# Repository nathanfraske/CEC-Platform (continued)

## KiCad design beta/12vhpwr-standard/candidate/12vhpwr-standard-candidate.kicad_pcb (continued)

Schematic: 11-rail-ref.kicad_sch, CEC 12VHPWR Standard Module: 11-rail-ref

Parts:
C22, C23: 100nF; C_0402_1005Metric; MPN CL05B104KO5NNNC; LCSC C1525
U4: REF3030; REF3030_DBZ3; MPN REF3030AIDBZR; LCSC C38423

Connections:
/VREF: C22.1, U4.2 (OUT); also elsewhere on the board

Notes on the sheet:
RAIL REF + SIDEBAND REF3030

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
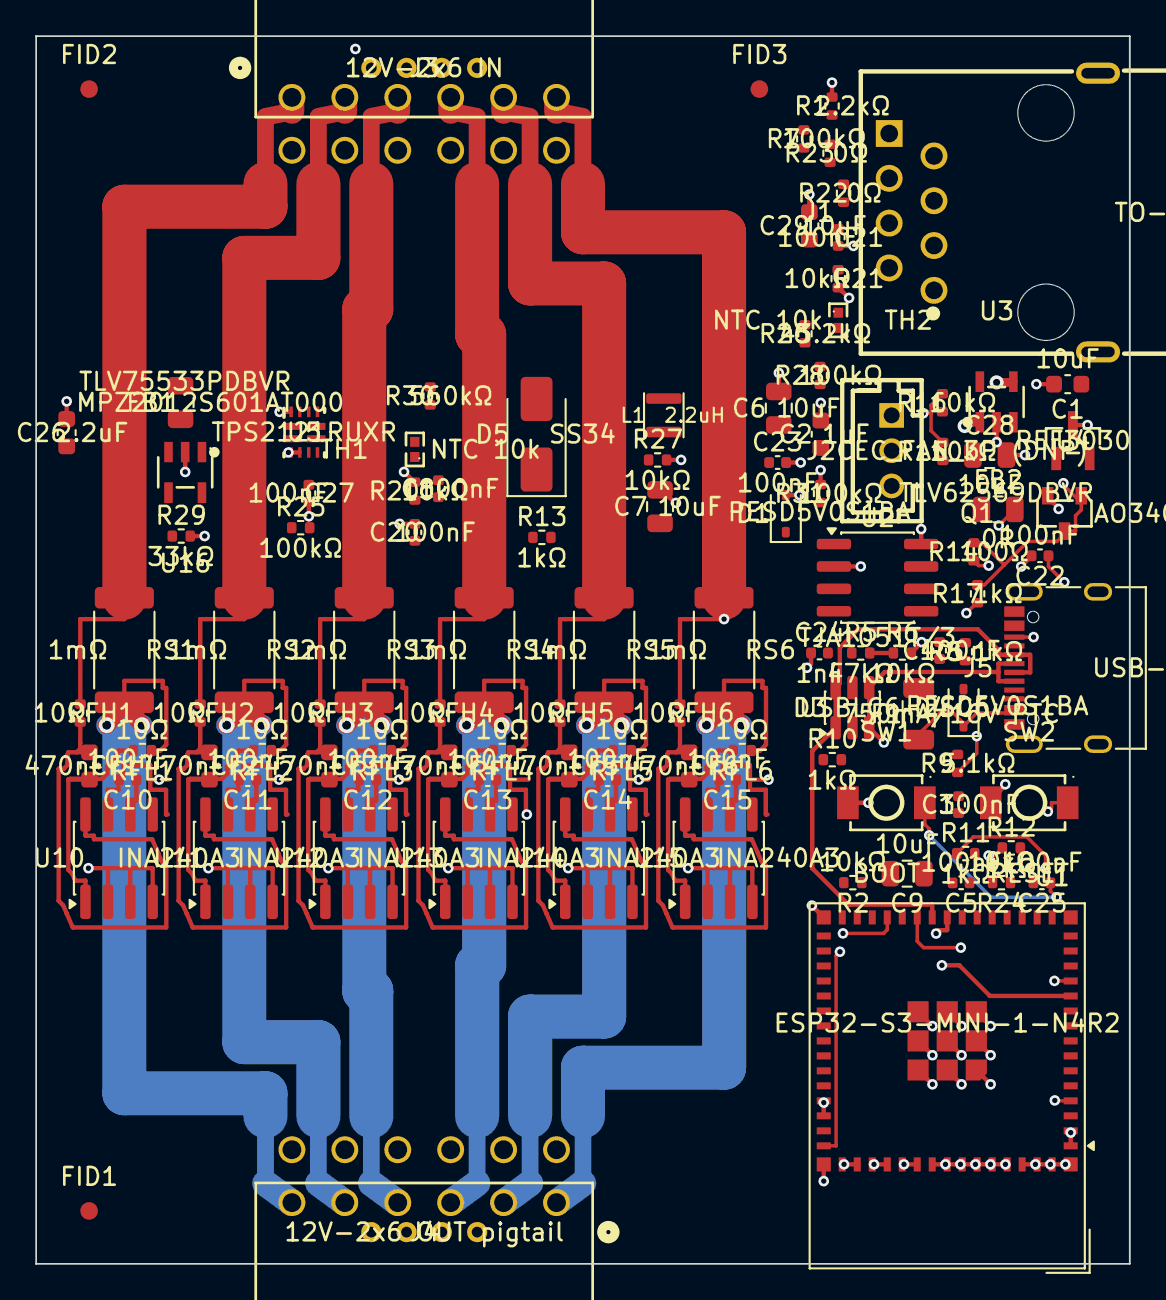
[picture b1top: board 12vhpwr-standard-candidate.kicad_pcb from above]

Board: 6 copper layers, 62.0 x 69.6 mm, 109 parts (0 on the bottom side), 74 nets.

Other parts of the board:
C29: 10uF; C_0603_1608Metric
FID1, FID2, FID3: Fiducial_1mm_Mask2mm
L1: 2.2uH; VLS252010HBX-2R2M-1
R30: 560kΩ; R_0402_1005Metric
R31: 100kΩ; R_0402_1005Metric
U3: TLV62569DBVR; SOT-23-5_L3.0-W1.7-P0.95-LS2.8-BL

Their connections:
+5VSB: U3.1, U3.4; also elsewhere on the board
/07-ldo/BUCK_FB_3V96: R30.2, R31.1, U3.5
/07-ldo/BUCK_SW_3V96: L1.1, U3.3

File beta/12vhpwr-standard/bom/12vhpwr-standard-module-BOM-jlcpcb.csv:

"Comment","Designator","Footprint","LCSC Part #"
"10uF","C1","cec-Capacitor_SMD:C_0603_1608Metric","C96446"
"1uF","C2","cec-Capacitor_SMD:C_0603_1608Metric","C29936"
"1nF","C24","cec-Capacitor_SMD:C_0402_1005Metric","C76947"
"2.2uF","C26","cec-Capacitor_SMD:C_0603_1608Metric","C23630"
"100nF","C3,C4,C5,C8,C10,C11,C12,C13,C14,C15,C20,C21,C22,C23,C25,C27","cec-Capacitor_SMD:C_0402_1005Metric","C1525"
"10uF","C6,C7,C9,C28","cec-Capacitor_SMD:C_0805_2012Metric","C15850"
"470nF","CF1,CF2,CF3,CF4,CF5,CF6","cec-Capacitor_SMD:C_0603_1608Metric","C1623"
"PESD5V0S1BA","D1,D4","cec-Diode_SMD:D_SOD-323","C5261083"
"USBLC6-2SC6","D3","cec-Package_TO_SOT_SMD:SOT-23-6","C2687116"
"SS34","D5","cec-Diode_SMD:D_SMA","C8678"
"750mA/16V PTC","F1","cec-Resistor_SMD:R_1206_3216Metric","C371166"
"MPZ2012S601AT000","FB1","cec-Capacitor_SMD:C_0805_2012Metric","C21519"
"0R","FB2","cec-Capacitor_SMD:C_0805_2012Metric","C17477"
"TO-HUB","J1","cec:RJ45_FTP_Shielded_Horizontal","C2683360"
"12V-2x6 IN","J3","cec:CEC_12V2x6_Horizontal",""
"12V-2x6 OUT pigtail","J4","cec:CEC_12V2x6_Horizontal",""
"USB-C 2.0","J5","cec-Connector_USB:USB_C_Receptacle_XKB_U262-16XN-4BVC11","C319148"
"AO3400A","Q1","cec-Package_TO_SOT_SMD:SOT-23-3_L2.9-W1.3-P1.90-LS2.4-BR","C20917"
"2.2kΩ","R1","cec-Resistor_SMD:R_0402_1005Metric","C25879"
"1kΩ","R10,R11,R12,R13,R17","cec-Resistor_SMD:R_0402_1005Metric","C11702"
"100Ω","R14","cec-Resistor_SMD:R_0402_1005Metric","C106233"
"10kΩ","R2,R15,R16,R20,R21,R24,R27","cec-Resistor_SMD:R_0402_1005Metric","C25744"
"0Ω","R22,R23","cec-Resistor_SMD:R_0402_1005Metric","C17168"
"43.2kΩ","R26","cec-Resistor_SMD:R_0402_1005Metric","C25894"
"33kΩ","R29","cec-Resistor_SMD:R_0402_1005Metric","C25779"
"47kΩ","R5","cec-Resistor_SMD:R_0402_1005Metric","C728561"
"10kΩ","R6","cec-Resistor_SMD:R_0402_1005Metric","C190095"
"100kΩ","R7,R25,R28","cec-Resistor_SMD:R_0402_1005Metric","C25741"
"5.1kΩ","R8,R9","cec-Resistor_SMD:R_0402_1005Metric","C25905"
"10Ω","RFH1,RFH2,RFH3,RFH4,RFH5,RFH6,RFL1,RFL2,RFL3,RFL4,RFL5,RFL6","cec-Resistor_SMD:R_0402_1005Metric","C705642"
"1mΩ","RS1,RS2,RS3,RS4,RS5,RS6","cec-Resistor_SMD:R_2512_6332Metric","C4175647"
"BOOT","SW1","cec-Button_Switch_SMD:TS-1088-AR02016","C720477"
"RESET","SW2","cec-Button_Switch_SMD:TS-1088-AR02016","C720477"
"NTC 10k","TH1,TH2","cec-Resistor_SMD:NTC_0402_1005Metric","C77131"
"ESP32-S3-MINI-1-N4R2","U1","cec-RF_Module:ESP32-S2-MINI-1_NoAntKeepout","C3013941"
"INA240A3","U10,U11,U12,U13,U14,U15","cec-Package_SO:SOIC-8_3.9x4.9mm_P1.27mm","C2060584"
"TLV75533PDRVR","U16","cec-Package_SON:WSON-6-1EP_2x2mm_P0.65mm_EP1x1.6mm","C2861750"
"TJA1051T/3","U2","cec-Package_SO:SOIC-8_3.9x4.9mm_P1.27mm","C38695"
"REF3030","U4","cec-Package_TO_SOT_SMD:REF3030_DBZ3","C38423"
"TPS2121RUXR","U5","cec-Package_DFN_QFN:RUX0012A","C485916"

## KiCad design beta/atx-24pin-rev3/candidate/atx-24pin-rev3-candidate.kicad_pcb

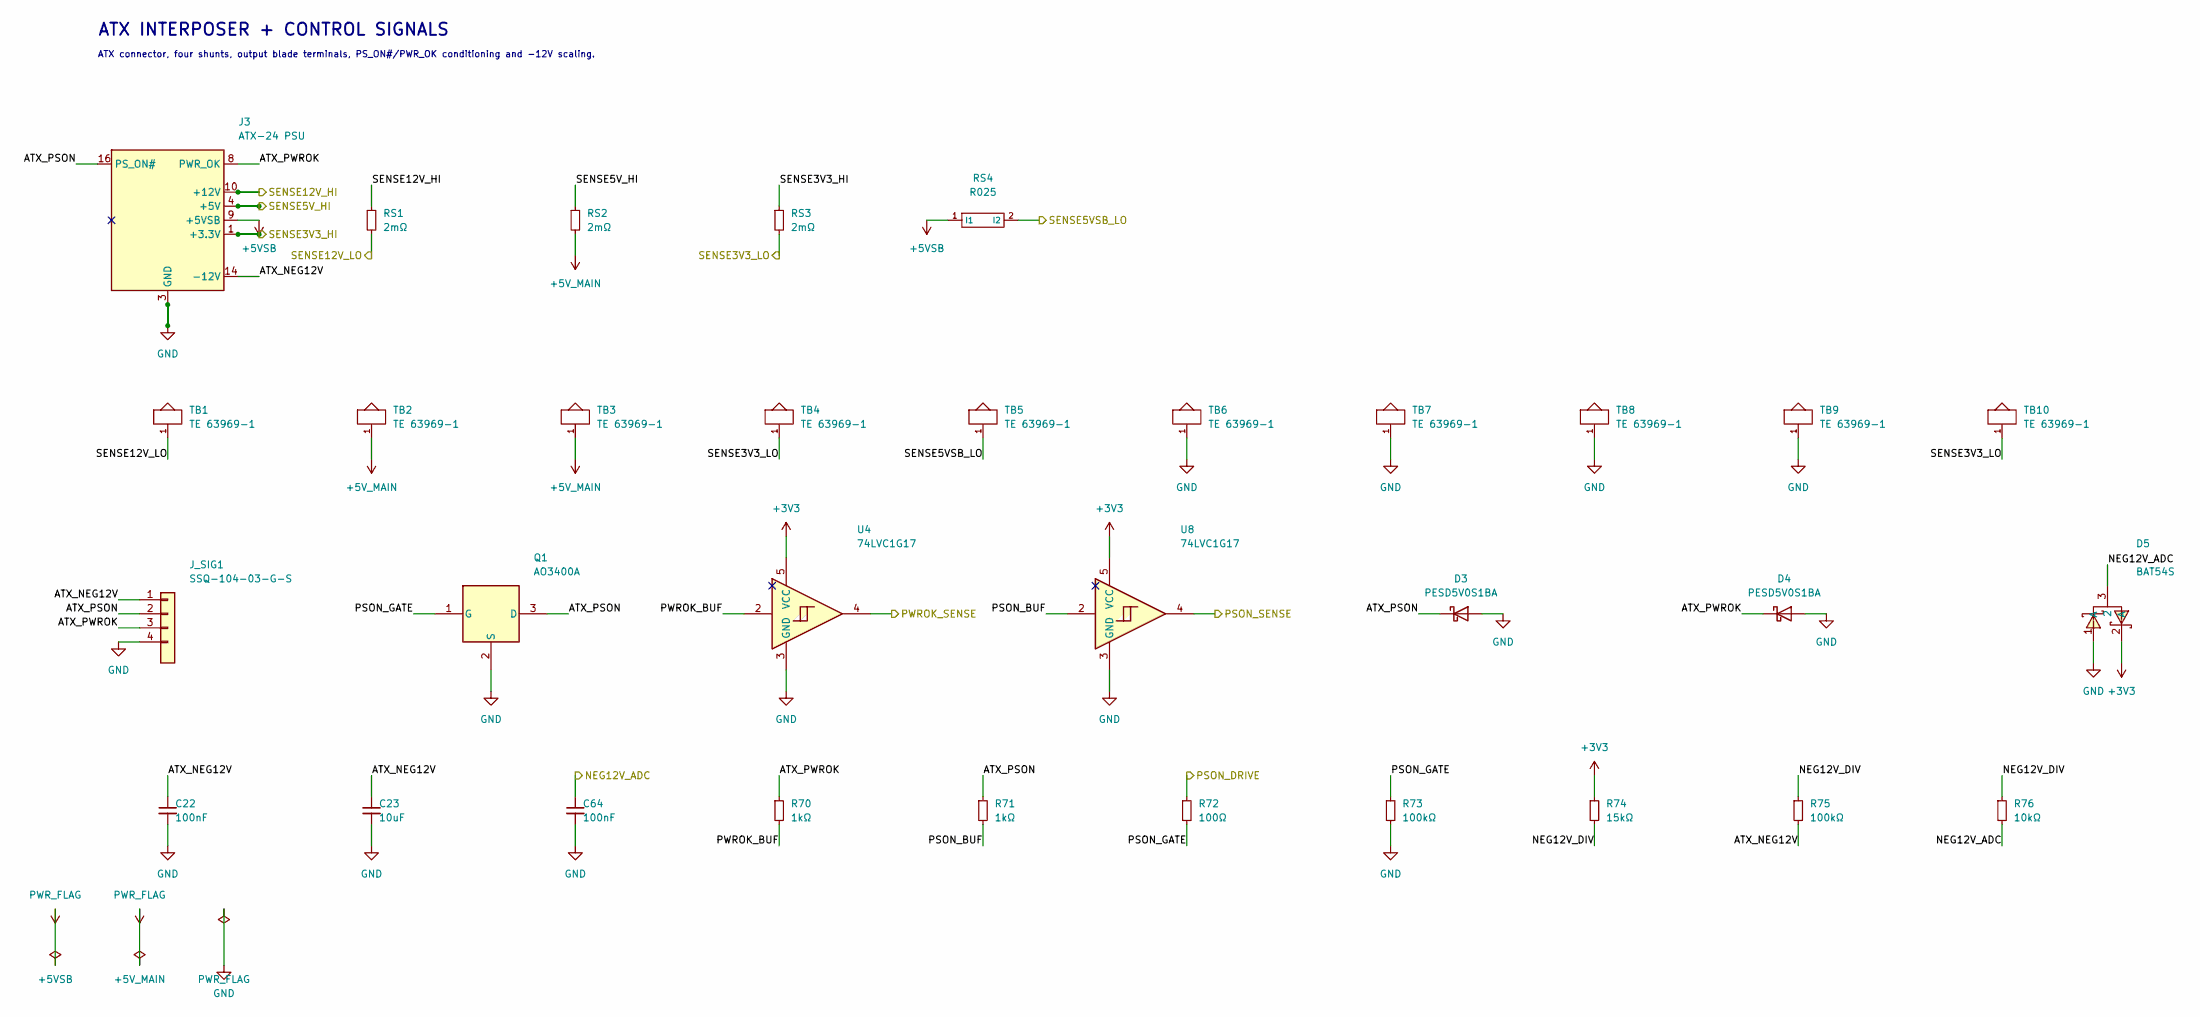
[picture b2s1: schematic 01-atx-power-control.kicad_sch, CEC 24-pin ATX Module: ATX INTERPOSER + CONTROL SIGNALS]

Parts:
C22, C64: 100nF; C_0402_1005Metric; MPN CL05B104KO5NNNC; LCSC C1525
C23: 10uF; C_0805_2012Metric; MPN CL21A106KAYNNNE; LCSC C15850
D3, D4: PESD5V0S1BA; D_SOD-323; MPN PESD5V0S1BA; LCSC C5261083
D5: BAT54S; SOT-23-3_L2.9-W1.3-P1.90-LS2.4-TL; MPN BAT54S; LCSC C545549
J3: ATX-24 PSU; Molex_Mini-Fit_Jr_5569-24A1_2x12_P4.20mm_Horizontal; MPN 39291247
J_SIG1: SSQ-104-03-G-S; PinSocket_1x04_P2.54mm_Vertical; MPN SSQ-104-03-G-S
Q1: AO3400A; SOT-23-3_L2.9-W1.3-P1.90-LS2.4-BR; MPN AO3400A; LCSC C20917
R70, R71: 1kΩ; R_0402_1005Metric; MPN 0402WGF1001TCE; LCSC C11702
R72: 100Ω; R_0402_1005Metric; MPN RC0402JR-07100RL; LCSC C106233
R73, R75: 100kΩ; R_0402_1005Metric; MPN 0402WGF1003TCE; LCSC C25741
R74: 15kΩ; R_0402_1005Metric; MPN 0402WGF1502TCE; LCSC C25756
R76: 10kΩ; R_0402_1005Metric; MPN 0402WGF1002TCE; LCSC C25744
RS1, RS2, RS3: 2mΩ; R_2512_6332Metric; MPN CSS2H-2512K-2L00F; LCSC C1729157
RS4: R025; R_2512_6332Metric; MPN LCSR2512FR025K9L; LCSC C494568
TB1, TB2, TB3, TB4, TB5, TB6, TB7, TB8, TB9, TB10: TE 63969-1; TE_63969_FASTON_Receptacle_250_Vertical_THT; MPN 63969-1; LCSC C2961150
U4, U8: 74LVC1G17; SOT-23-5; MPN SN74LVC1G17DBVR; LCSC C7836

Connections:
+3V3: D5.2 (A), R74.1, U4.5 (VCC), U8.5 (VCC); also elsewhere on the board
+5VSB: J3.9 (+5VSB), RS4.1 (I1); also elsewhere on the board
+5V_MAIN: RS2.2, TB2.1, TB3.1; also elsewhere on the board
/ATX INTERPOSER + CONTROL SIGNALS/ATX_NEG12V: C22.1, C23.1, J3.14 (-12V), J_SIG1.1, R75.2
/ATX INTERPOSER + CONTROL SIGNALS/ATX_PSON: D3.1 (K), J3.16 (PS_ON#), J_SIG1.2, Q1.3 (D), R71.1
/ATX INTERPOSER + CONTROL SIGNALS/ATX_PWROK: D4.1 (K), J3.8 (PWR_OK), J_SIG1.3, R70.1
/ATX INTERPOSER + CONTROL SIGNALS/NEG12V_DIV: R74.2, R75.1, R76.1
/ATX INTERPOSER + CONTROL SIGNALS/PSON_BUF: R71.2, U8.2
/ATX INTERPOSER + CONTROL SIGNALS/PSON_GATE: Q1.1 (G), R72.2, R73.1
/ATX INTERPOSER + CONTROL SIGNALS/PWROK_BUF: R70.2, U4.2
/NEG12V_ADC: C64.1, D5.3 (2), R76.2; also elsewhere on the board
/PSON_DRIVE: R72.1; also elsewhere on the board
/PSON_SENSE: U8.4; also elsewhere on the board
/PWROK_SENSE: U4.4; also elsewhere on the board
/SENSE3V3_HI: J3.1 (+3.3V), J3.2 (+3.3V), J3.12 (+3.3V), J3.13 (+3.3V), RS3.1; also elsewhere on the board
/SENSE3V3_LO: RS3.2, TB4.1, TB10.1; also elsewhere on the board
/SENSE5VSB_LO: RS4.2 (I2), TB5.1; also elsewhere on the board
/SENSE5V_HI: J3.4 (+5V), J3.6 (+5V), J3.21 (+5V), J3.22 (+5V), J3.23 (+5V), RS2.1; also elsewhere on the board
/SENSE12V_HI: J3.10 (+12V), J3.11 (+12V), RS1.1; also elsewhere on the board
/SENSE12V_LO: RS1.2, TB1.1; also elsewhere on the board
GND: C22.2, C23.2, C64.2, D3.2 (A), D4.2 (A), D5.1 (A), J3.3 (GND), J3.5 (GND), J3.7 (GND), J3.15 (GND), J3.17 (GND), J3.18 (GND), J3.19 (GND), J3.24 (GND), J_SIG1.4, Q1.2 (S), R73.2, TB6.1, TB7.1, TB8.1, TB9.1, U4.3 (GND), U8.3 (GND); also elsewhere on the board

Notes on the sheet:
ATX INTERPOSER + CONTROL SIGNALS
ATX connector, four shunts, output blade terminals, PS_ON#/PWR_OK conditioning and -12V scaling.

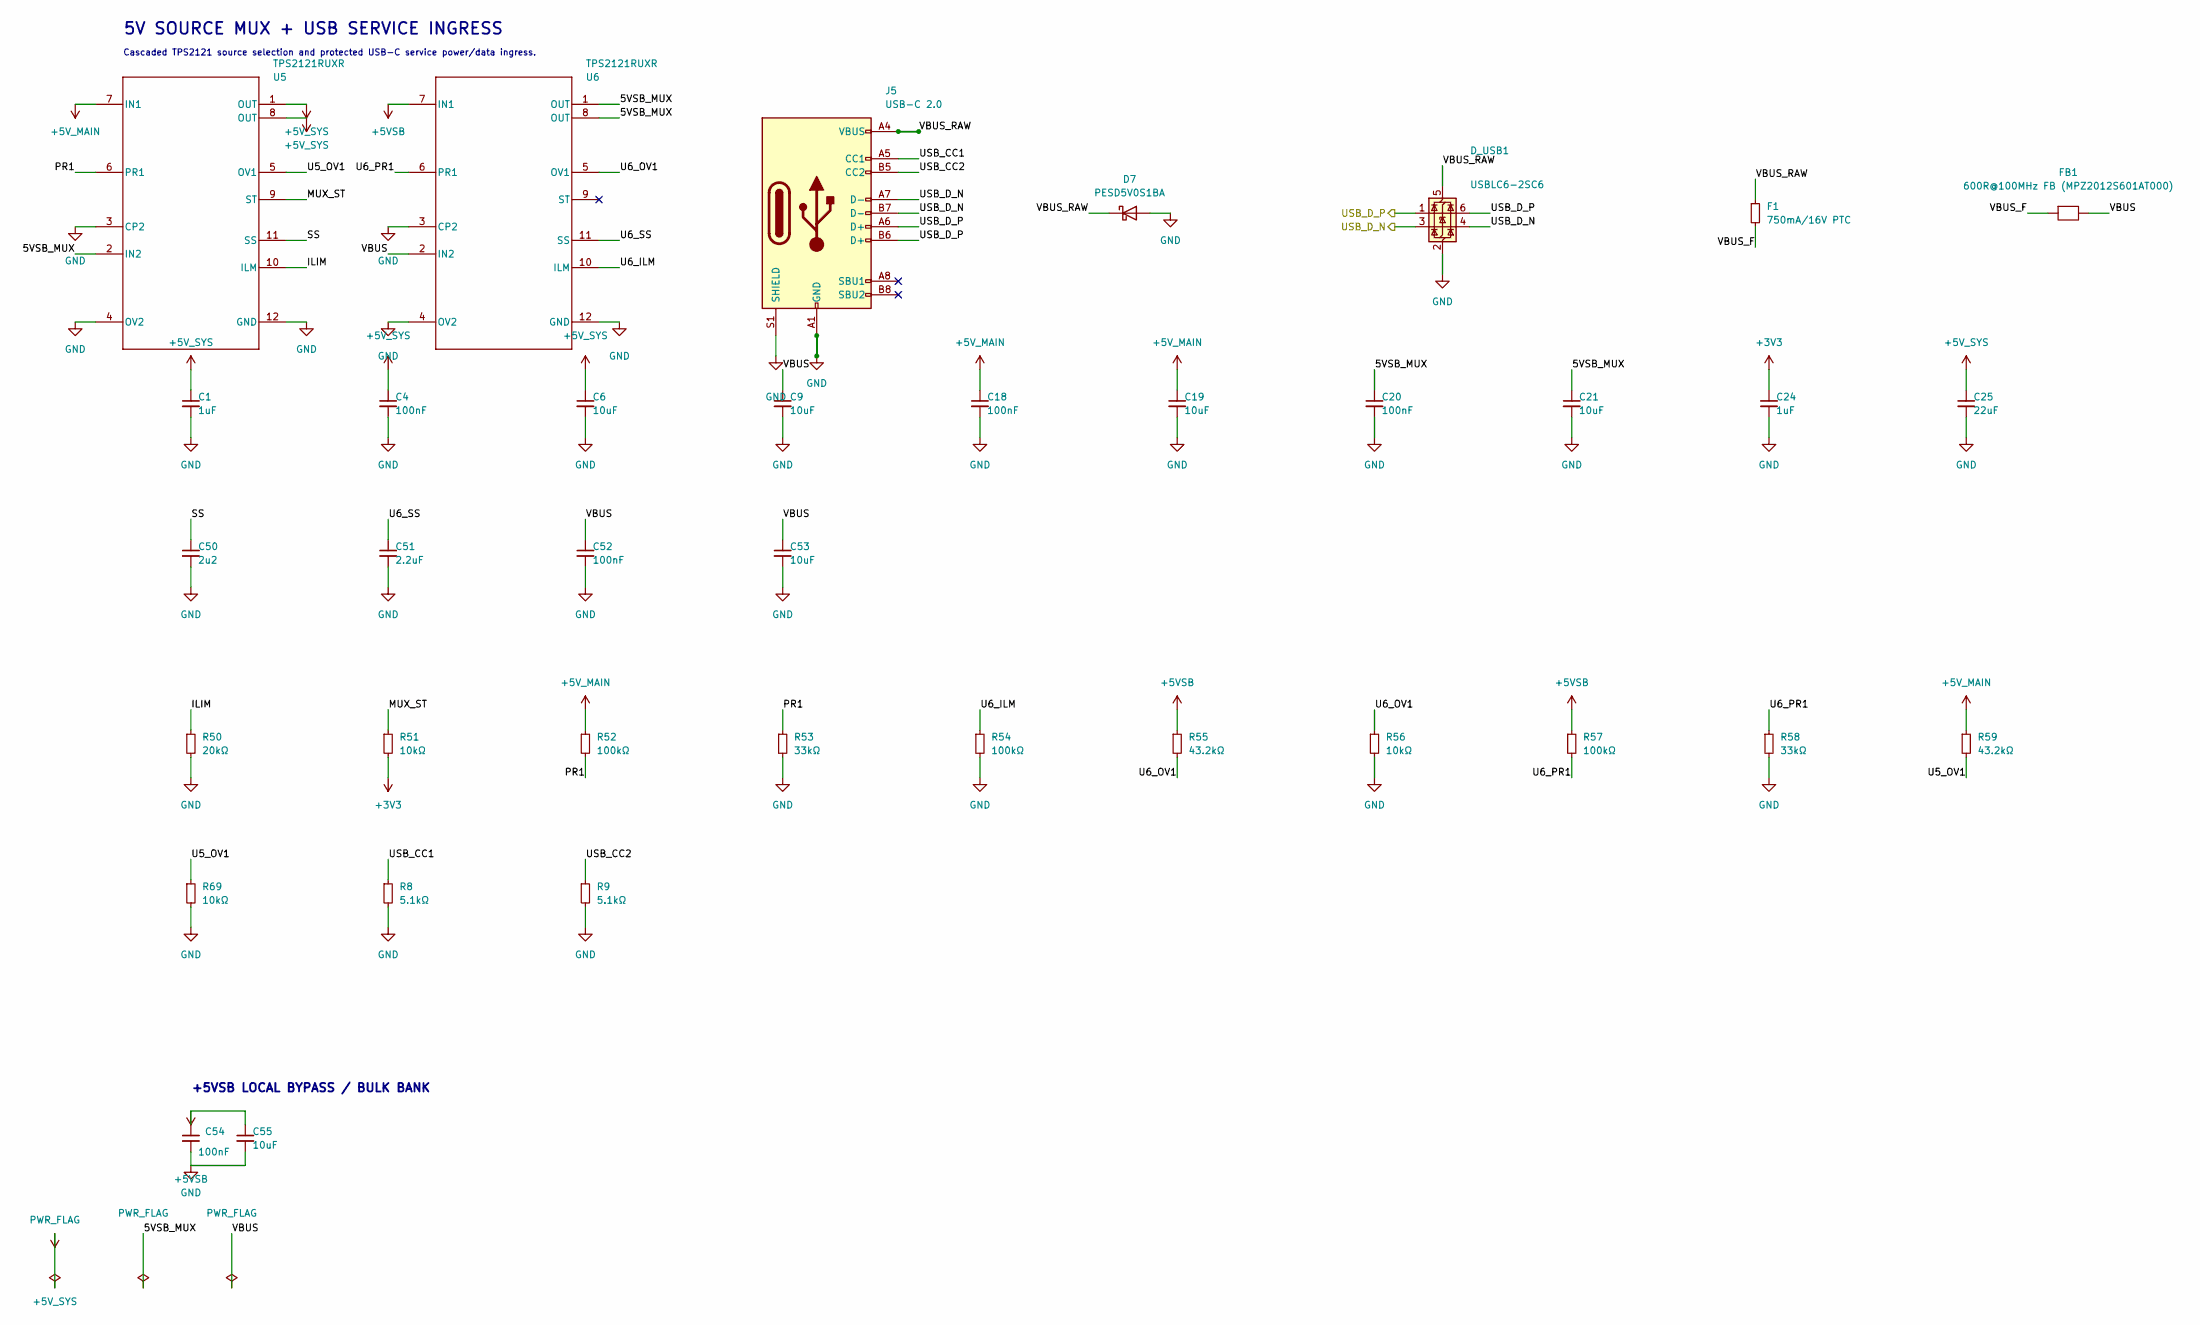
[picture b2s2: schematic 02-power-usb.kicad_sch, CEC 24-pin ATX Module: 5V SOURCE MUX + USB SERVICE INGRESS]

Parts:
C1, C24: 1uF; C_0603_1608Metric; MPN CL10B105KA8NNNC; LCSC C29936
C4, C18, C20, C52, C54: 100nF; C_0402_1005Metric; MPN CL05B104KO5NNNC; LCSC C1525
C6, C9, C19, C21, C53, C55: 10uF; C_0805_2012Metric; MPN CL21A106KAYNNNE; LCSC C15850
C25: 22uF; C_0805_2012Metric; MPN CL21A226MAQNNNE; LCSC C45783
C50: 2u2; C_0603_1608Metric; MPN CL10A225KO8NNNC; LCSC C23630
C51: 2.2uF; C_0603_1608Metric; MPN CL10A225KO8NNNC; LCSC C23630
D7: PESD5V0S1BA; D_SOD-323; MPN PESD5V0S1BA; LCSC C5261083
D_USB1: USBLC6-2SC6; SOT-23-6; MPN USBLC6-2SC6; LCSC C7519
F1: 750mA/16V PTC; R_1206_3216Metric; MPN 1206L075/16WR; LCSC C371166
FB1: 600R@100MHz FB (MPZ2012S601AT000); C_0805_2012Metric; MPN MPZ2012S601AT000; LCSC C21519
J5: USB-C 2.0; USB_C_Receptacle_XKB_U262-16XN-4BVC11; MPN U262-161N-4BVC11; LCSC C319148
R8, R9: 5.1kΩ; R_0402_1005Metric; MPN 0402WGF5101TCE; LCSC C25905
R50: 20kΩ; R_0402_1005Metric; MPN 0402WGF2002TCE; LCSC C25765
R51, R56, R69: 10kΩ; R_0402_1005Metric; MPN 0402WGF1002TCE; LCSC C25744
R52, R54, R57: 100kΩ; R_0402_1005Metric; MPN 0402WGF1003TCE; LCSC C25741
R53, R58: 33kΩ; R_0402_1005Metric; MPN 0402WGF3302TCE; LCSC C25779
R55, R59: 43.2kΩ; R_0402_1005Metric; MPN 0402WGF4322TCE; LCSC C25894
U5, U6: TPS2121RUXR; RUX0012A; MPN TPS2121RUXR; LCSC C485916

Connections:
+3V3: C24.1, R51.2; also elsewhere on the board
+5VSB: C54.1, C55.1, R55.1, R57.1, U6.7 (IN1); also elsewhere on the board
+5V_MAIN: C18.1, C19.1, R52.1, R59.1, U5.7 (IN1); also elsewhere on the board
+5V_SYS: C1.1, C4.1, C6.1, C25.1, U5.1 (OUT), U5.8 (OUT); also elsewhere on the board
/5V SOURCE MUX + USB SERVICE INGRESS/5VSB_MUX: C20.1, C21.1, U5.2 (IN2), U6.1 (OUT), U6.8 (OUT)
/5V SOURCE MUX + USB SERVICE INGRESS/ILIM: R50.1, U5.10 (ILM)
/5V SOURCE MUX + USB SERVICE INGRESS/MUX_ST: R51.1, U5.9 (ST)
/5V SOURCE MUX + USB SERVICE INGRESS/PR1: R52.2, R53.1, U5.6 (PR1)
/5V SOURCE MUX + USB SERVICE INGRESS/SS: C50.1, U5.11 (SS)
/5V SOURCE MUX + USB SERVICE INGRESS/U5_OV1: R59.2, R69.1, U5.5 (OV1)
/5V SOURCE MUX + USB SERVICE INGRESS/U6_ILM: R54.1, U6.10 (ILM)
/5V SOURCE MUX + USB SERVICE INGRESS/U6_OV1: R55.2, R56.1, U6.5 (OV1)
/5V SOURCE MUX + USB SERVICE INGRESS/U6_PR1: R57.2, R58.1, U6.6 (PR1)
/5V SOURCE MUX + USB SERVICE INGRESS/U6_SS: C51.1, U6.11 (SS)
/5V SOURCE MUX + USB SERVICE INGRESS/USB_CC1: J5.A5 (CC1), R8.1
/5V SOURCE MUX + USB SERVICE INGRESS/USB_CC2: J5.B5 (CC2), R9.1
/5V SOURCE MUX + USB SERVICE INGRESS/VBUS: C9.1, C52.1, C53.1, FB1.2, U6.2 (IN2)
/5V SOURCE MUX + USB SERVICE INGRESS/VBUS_F: F1.2, FB1.1
/5V SOURCE MUX + USB SERVICE INGRESS/VBUS_RAW: D7.1 (K), D_USB1.5 (VBUS), F1.1, J5.A4 (VBUS), J5.A9 (VBUS), J5.B4 (VBUS), J5.B9 (VBUS)
/USB_D_N: D_USB1.3 (I/O2), D_USB1.4 (I/O2), J5.A7 (D-), J5.B7 (D-); also elsewhere on the board
/USB_D_P: D_USB1.1 (I/O1), D_USB1.6 (I/O1), J5.A6 (D+), J5.B6 (D+); also elsewhere on the board
GND: C1.2, C4.2, C6.2, C9.2, C18.2, C19.2, C20.2, C21.2, C24.2, C25.2, C50.2, C51.2, C52.2, C53.2, C54.2, C55.2, D7.2 (A), D_USB1.2 (GND), J5.A1 (GND), J5.A12 (GND), J5.B1 (GND), J5.B12 (GND), J5.S1 (SHIELD), R8.2, R9.2, R50.2, R53.2, R54.2, R56.2, R58.2, R69.2, U5.3 (CP2), U5.4 (OV2), U5.12 (GND), U6.3 (CP2), U6.4 (OV2), U6.12 (GND); also elsewhere on the board

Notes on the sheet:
5V SOURCE MUX + USB SERVICE INGRESS
Cascaded TPS2121 source selection and protected USB-C service power/data ingress.
+5VSB LOCAL BYPASS / BULK BANK

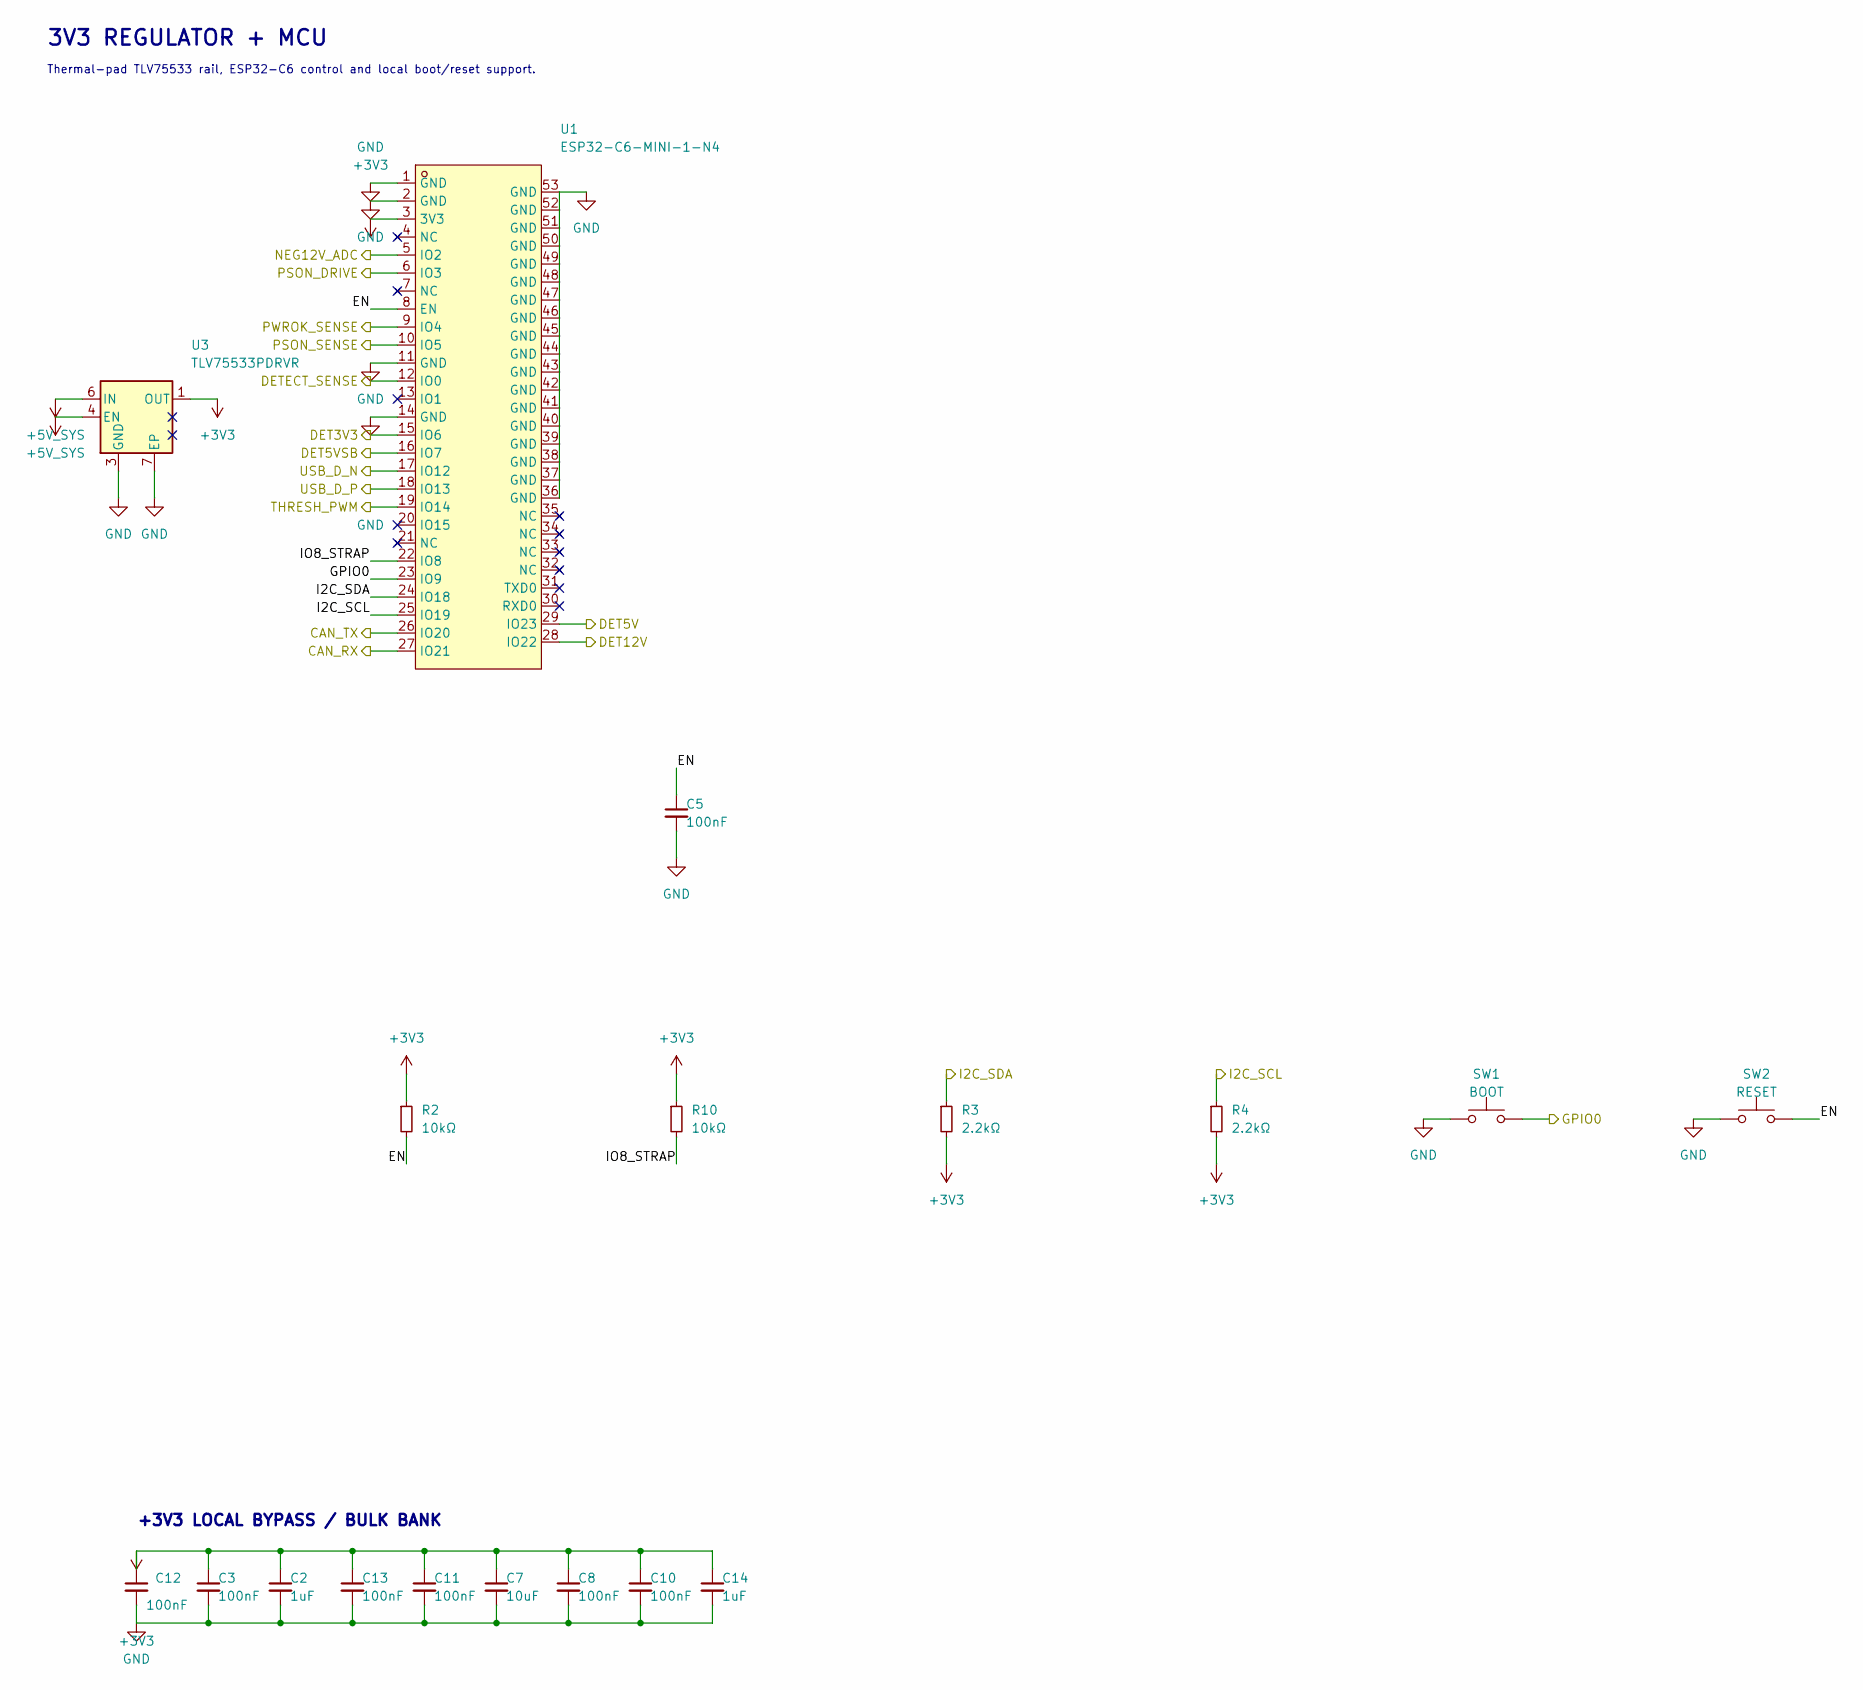
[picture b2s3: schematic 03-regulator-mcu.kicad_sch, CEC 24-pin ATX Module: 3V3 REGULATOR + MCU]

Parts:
C2, C14: 1uF; C_0603_1608Metric; MPN CL10B105KA8NNNC; LCSC C29936
C3, C5, C8, C10, C11, C12, C13: 100nF; C_0402_1005Metric; MPN CL05B104KO5NNNC; LCSC C1525
C7: 10uF; C_0805_2012Metric; MPN CL21A106KAYNNNE; LCSC C15850
R2, R10: 10kΩ; R_0402_1005Metric; MPN 0402WGF1002TCE; LCSC C25744
R3, R4: 2.2kΩ; R_0402_1005Metric; MPN 0402WGF2201TCE; LCSC C25879
SW1: BOOT; TS-1088-AR02016; MPN TS-1088-AR02016; LCSC C720477
SW2: RESET; TS-1088-AR02016; MPN TS-1088-AR02016; LCSC C720477
U1: ESP32-C6-MINI-1-N4; ESP32-C6-MINI-1; MPN ESP32-C6-MINI-1-N4; LCSC C5736265
U3: TLV75533PDRVR; WSON-6-1EP_2x2mm_P0.65mm_EP1x1.6mm; MPN TLV75533PDRVR; LCSC C2861750

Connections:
+3V3: C2.1, C3.1, C7.1, C8.1, C10.1, C11.1, C12.1, C13.1, C14.1, R2.1, R3.2, R4.2, R10.1, U1.3 (3V3), U3.1 (OUT); also elsewhere on the board
+5V_SYS: U3.4 (EN), U3.6 (IN); also elsewhere on the board
/3V3 REGULATOR + MCU/EN: C5.1, R2.2, SW2.2, U1.8 (EN)
/3V3 REGULATOR + MCU/IO8_STRAP: R10.2, U1.22 (IO8)
/CAN_RX: U1.27 (IO21); also elsewhere on the board
/CAN_TX: U1.26 (IO20); also elsewhere on the board
/DET3V3: U1.15 (IO6); also elsewhere on the board
/DET5V: U1.29 (IO23); also elsewhere on the board
/DET5VSB: U1.16 (IO7); also elsewhere on the board
/DET12V: U1.28 (IO22); also elsewhere on the board
/DETECT_SENSE: U1.12 (IO0); also elsewhere on the board
/GPIO0: SW1.2, U1.23 (IO9); also elsewhere on the board
/I2C_SCL: R4.1, U1.25 (IO19); also elsewhere on the board
/I2C_SDA: R3.1, U1.24 (IO18); also elsewhere on the board
/NEG12V_ADC: U1.5 (IO2); also elsewhere on the board
/PSON_DRIVE: U1.6 (IO3); also elsewhere on the board
/PSON_SENSE: U1.10 (IO5); also elsewhere on the board
/PWROK_SENSE: U1.9 (IO4); also elsewhere on the board
/THRESH_PWM: U1.19 (IO14); also elsewhere on the board
/USB_D_N: U1.17 (IO12); also elsewhere on the board
/USB_D_P: U1.18 (IO13); also elsewhere on the board
GND: C2.2, C3.2, C5.2, C7.2, C8.2, C10.2, C11.2, C12.2, C13.2, C14.2, SW1.1, SW2.1, U1.1 (GND), U1.2 (GND), U1.11 (GND), U1.14 (GND), U1.36 (GND), U1.37 (GND), U1.38 (GND), U1.39 (GND), U1.40 (GND), U1.41 (GND), U1.42 (GND), U1.43 (GND), U1.44 (GND), U1.45 (GND), U1.46 (GND), U1.47 (GND), U1.48 (GND), U1.49 (GND), U1.50 (GND), U1.51 (GND), U1.52 (GND), U1.53 (GND), U3.3 (GND), U3.7 (EP); also elsewhere on the board

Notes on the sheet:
3V3 REGULATOR + MCU
Thermal-pad TLV75533 rail, ESP32-C6 control and local boot/reset support.
+3V3 LOCAL BYPASS / BULK BANK

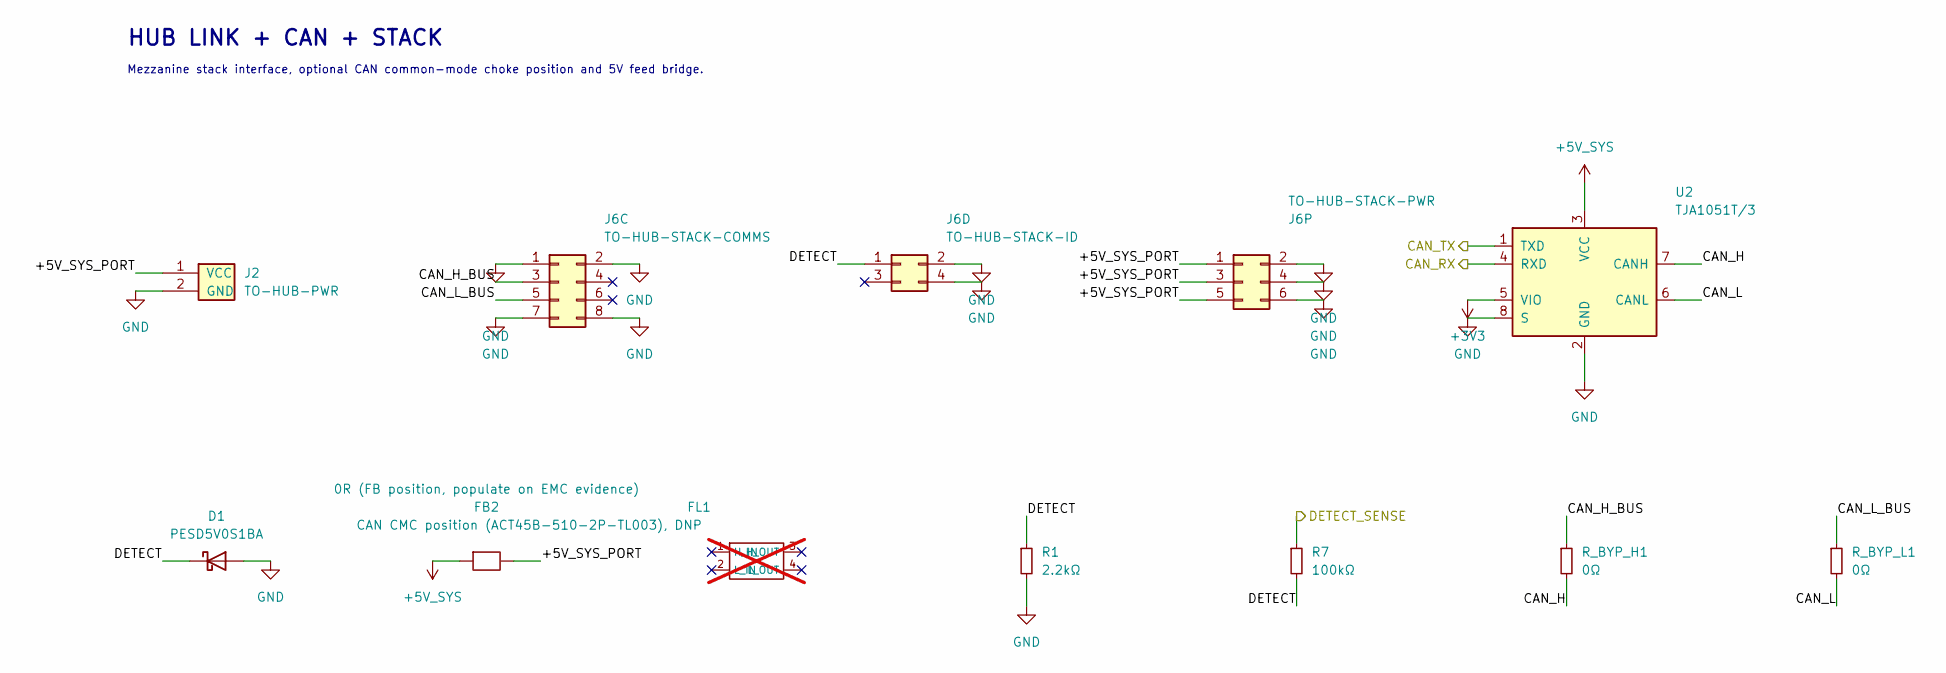
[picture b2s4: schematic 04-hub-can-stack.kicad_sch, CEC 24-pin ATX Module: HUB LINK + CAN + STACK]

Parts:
D1: PESD5V0S1BA; D_SOD-323; MPN PESD5V0S1BA; LCSC C5261083
FB2: 0R (FB position, populate on EMC evidence); C_0805_2012Metric; MPN 0805W8F0000T5E; LCSC C17477
FL1: CAN CMC position (ACT45B-510-2P-TL003), DNP; MPN ACT45B-510-2P-TL003; LCSC C76584; not fitted
J2: TO-HUB-PWR; JST_XH_S2B-XH-A_1x02_P2.50mm_Horizontal; MPN S2B-XH-A(LF)(SN); LCSC C157931
J6C: TO-HUB-STACK-COMMS; PinHeader_2x04_P2.54mm_Vertical; MPN TSW-104-17-G-D
J6D: TO-HUB-STACK-ID; PinHeader_2x02_P2.54mm_Vertical; MPN TSW-102-17-G-D
J6P: TO-HUB-STACK-PWR; PinHeader_2x03_P2.54mm_Vertical; MPN TSW-103-17-G-D
R1: 2.2kΩ; R_0402_1005Metric; MPN 0402WGF2201TCE; LCSC C25879
R7: 100kΩ; R_0402_1005Metric; MPN 0402WGF1003TCE; LCSC C25741
R_BYP_H1: 0Ω; R_0402_1005Metric; MPN 0402WGF0000TCE; LCSC C17168
R_BYP_L1: 0Ω; R_0402_1005Metric; MPN 0402WGF0000TCE; LCSC C17168
U2: TJA1051T/3; SOIC-8_3.9x4.9mm_P1.27mm; MPN TJA1051T/3/1J; LCSC C38695

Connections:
+3V3: U2.5 (VIO); also elsewhere on the board
+5V_SYS: FB2.1, U2.3 (VCC); also elsewhere on the board
/CAN_RX: U2.4 (RXD); also elsewhere on the board
/CAN_TX: U2.1 (TXD); also elsewhere on the board
/DETECT_SENSE: R7.1; also elsewhere on the board
/HUB LINK + CAN + STACK/+5V_SYS_PORT: FB2.2, J2.1 (VCC), J6P.1, J6P.3, J6P.5
/HUB LINK + CAN + STACK/CAN_H: R_BYP_H1.2, U2.7 (CANH)
/HUB LINK + CAN + STACK/CAN_H_BUS: J6C.3, R_BYP_H1.1
/HUB LINK + CAN + STACK/CAN_L: R_BYP_L1.2, U2.6 (CANL)
/HUB LINK + CAN + STACK/CAN_L_BUS: J6C.5, R_BYP_L1.1
/HUB LINK + CAN + STACK/DETECT: D1.1 (K), J6D.1, R1.1, R7.2
GND: D1.2 (A), J2.2 (GND), J6C.1, J6C.2, J6C.7, J6C.8, J6D.2, J6D.4, J6P.2, J6P.4, J6P.6, R1.2, U2.2 (GND), U2.8 (S); also elsewhere on the board

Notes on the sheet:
HUB LINK + CAN + STACK
Mezzanine stack interface, optional CAN common-mode choke position and 5V feed bridge.
